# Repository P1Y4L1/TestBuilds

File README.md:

# TestBuilds
These are my PCB Test Builds which will updated , if intrested you are free to browse and fork from it.

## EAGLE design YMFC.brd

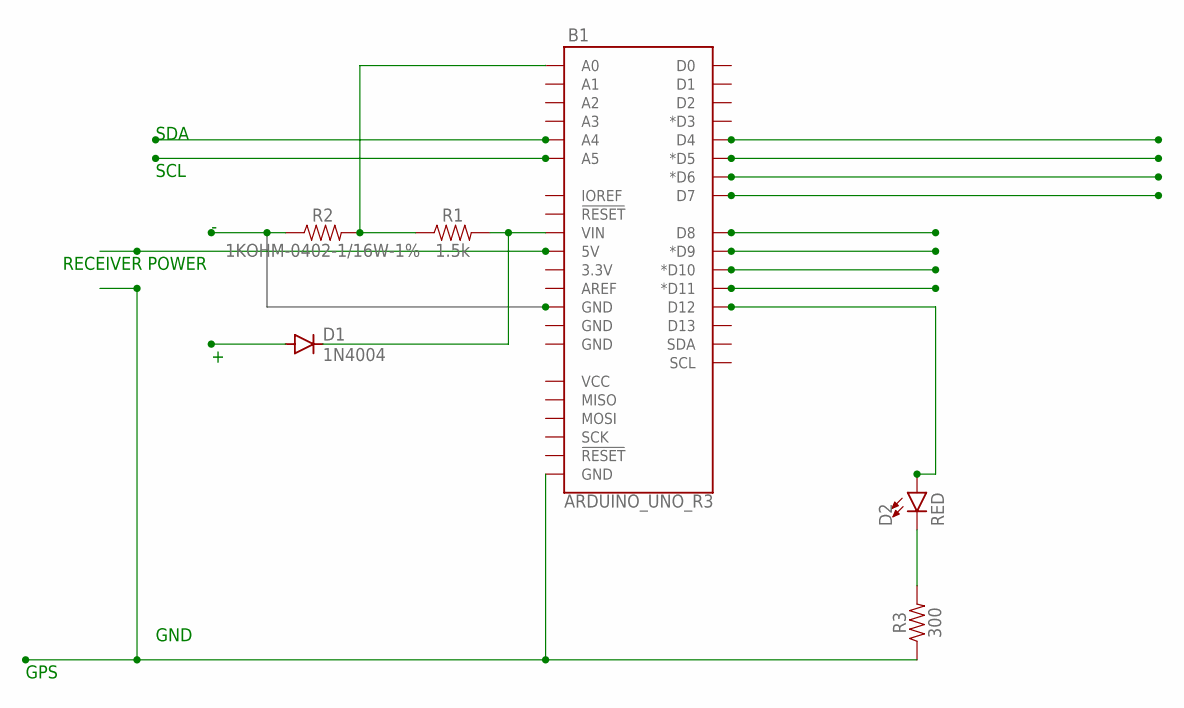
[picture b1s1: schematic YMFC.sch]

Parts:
B1: ARDUINO_UNO_R3; ARDUINO_R3
D1: 1N4004; DO41-10
D2: RED; LED-0603
R1: 1.5k; 0603
R2: 1KOHM-0402-1/16W-1%; 0402
R3: 300; 0603

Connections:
unnamed: B1.VIN, D1.C, R1.2
unnamed: B1.A0, R1.1, R2.2
unnamed: B1.D12, D2.A
unnamed: D2.C, R3.2
unnamed: B1.GND@1 (GND), R3.1

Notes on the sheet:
SDA
SCL
RECEIVER POWER
GND
GPS

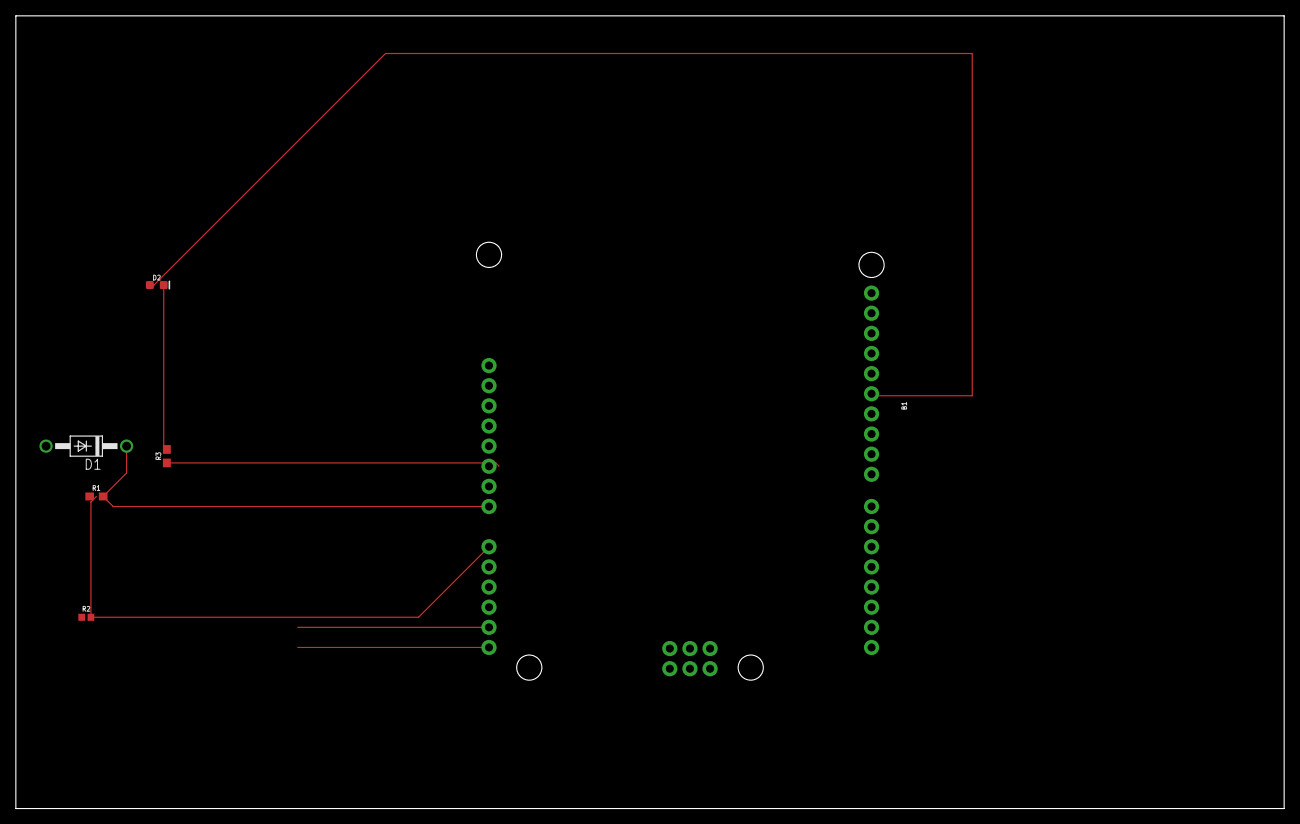
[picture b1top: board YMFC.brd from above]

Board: 2 copper layers, 160.0 x 100.0 mm, 6 parts (0 on the bottom side), 5 nets.

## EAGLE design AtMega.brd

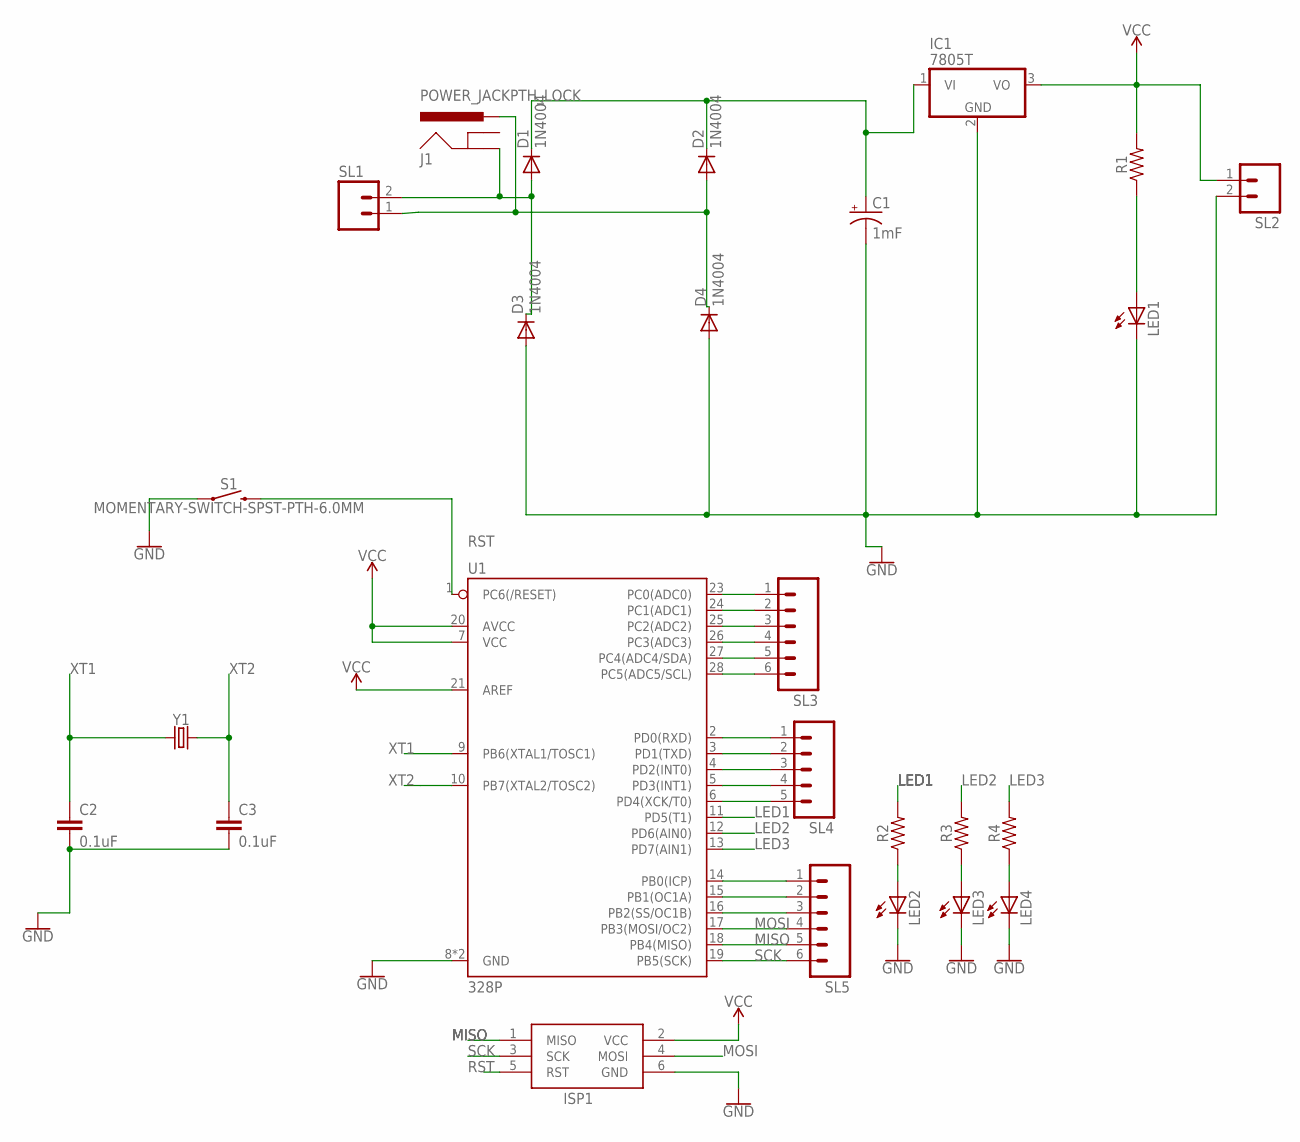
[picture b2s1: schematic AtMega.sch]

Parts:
C1: 1mF; CPOL-RADIAL-5MM-10MM
C2, C3: 0.1uF; CAP-PTH-SMALL-KIT
D1, D2, D3, D4: 1N4004; DO41-10
IC1: 7805T; TO220H
ISP1: AVRISP-6; AVRISP
J1: POWER_JACKPTH_LOCK; POWER_JACK_PTH_LOCK
LED1: LED5MM
LED2, LED3, LED4: LED3MM
R1, R2, R3, R4: AXIAL-0.3
S1: MOMENTARY-SWITCH-SPST-PTH-6.0MM; TACTILE_SWITCH_PTH_6.0MM
SL1, SL2: M02; 02P
SL3, SL5: M06; 06P
SL4: M05; 05P
U1: 328P; DIP28
Y1: CRYSTALPTH-HC49US; HC49US

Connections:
GND: C1.-, C2.2, C3.2, D3.A, IC1.2 (GND), ISP1.6 (GND), LED1.K (C), LED2.K (C), LED3.K (C), LED4.K (C), S1.1, SL2.2, U1.8 (GND), U1.22 (GND)
LED1: R2.P$2 (2), U1.11 (PD5(T1))
LED2: R3.P$2 (2), U1.12 (PD6(AIN0))
LED3: R4.P$2 (2), U1.13 (PD7(AIN1))
MISO: ISP1.1 (MISO), SL5.5, U1.18 (PB4(MISO))
MOSI: ISP1.4 (MOSI), SL5.4, U1.17 (PB3(MOSI/OC2))
unnamed: D2.A, D4.C, J1.PWR, SL1.1
unnamed: SL5.3, U1.16 (PB2(SS/OC1B))
unnamed: LED4.A, R4.P$1 (1)
unnamed: C1.+, D1.C, D2.C, IC1.1 (VI)
unnamed: D1.A, D3.C, SL1.2
unnamed: LED1.A, R1.P$1 (1)
unnamed: LED3.A, R3.P$1 (1)
unnamed: LED2.A, R2.P$1 (1)
unnamed: SL3.1, U1.23 (PC0(ADC0))
unnamed: SL3.2, U1.24 (PC1(ADC1))
unnamed: SL3.3, U1.25 (PC2(ADC2))
unnamed: SL3.4, U1.26 (PC3(ADC3))
unnamed: SL3.5, U1.27 (PC4(ADC4/SDA))
unnamed: SL3.6, U1.28 (PC5(ADC5/SCL))
unnamed: SL4.1, U1.2 (PD0(RXD))
unnamed: SL4.2, U1.3 (PD1(TXD))
unnamed: SL4.3, U1.4 (PD2(INT0))
unnamed: SL4.4, U1.5 (PD3(INT1))
unnamed: SL4.5, U1.6 (PD4(XCK/T0))
unnamed: SL5.1, U1.14 (PB0(ICP))
unnamed: SL5.2, U1.15 (PB1(OC1A))
RST: ISP1.5 (RST), S1.3 (2), U1.1 (PC6(/RESET))
SCK: ISP1.3 (SCK), SL5.6, U1.19 (PB5(SCK))
VCC: IC1.3 (VO), ISP1.2 (VCC), R1.P$2 (2), SL2.1, U1.7 (VCC), U1.20 (AVCC), U1.21 (AREF)
XT1: C2.1, U1.9 (PB6(XTAL1/TOSC1)), Y1.1
XT2: C3.1, U1.10 (PB7(XTAL2/TOSC2)), Y1.2

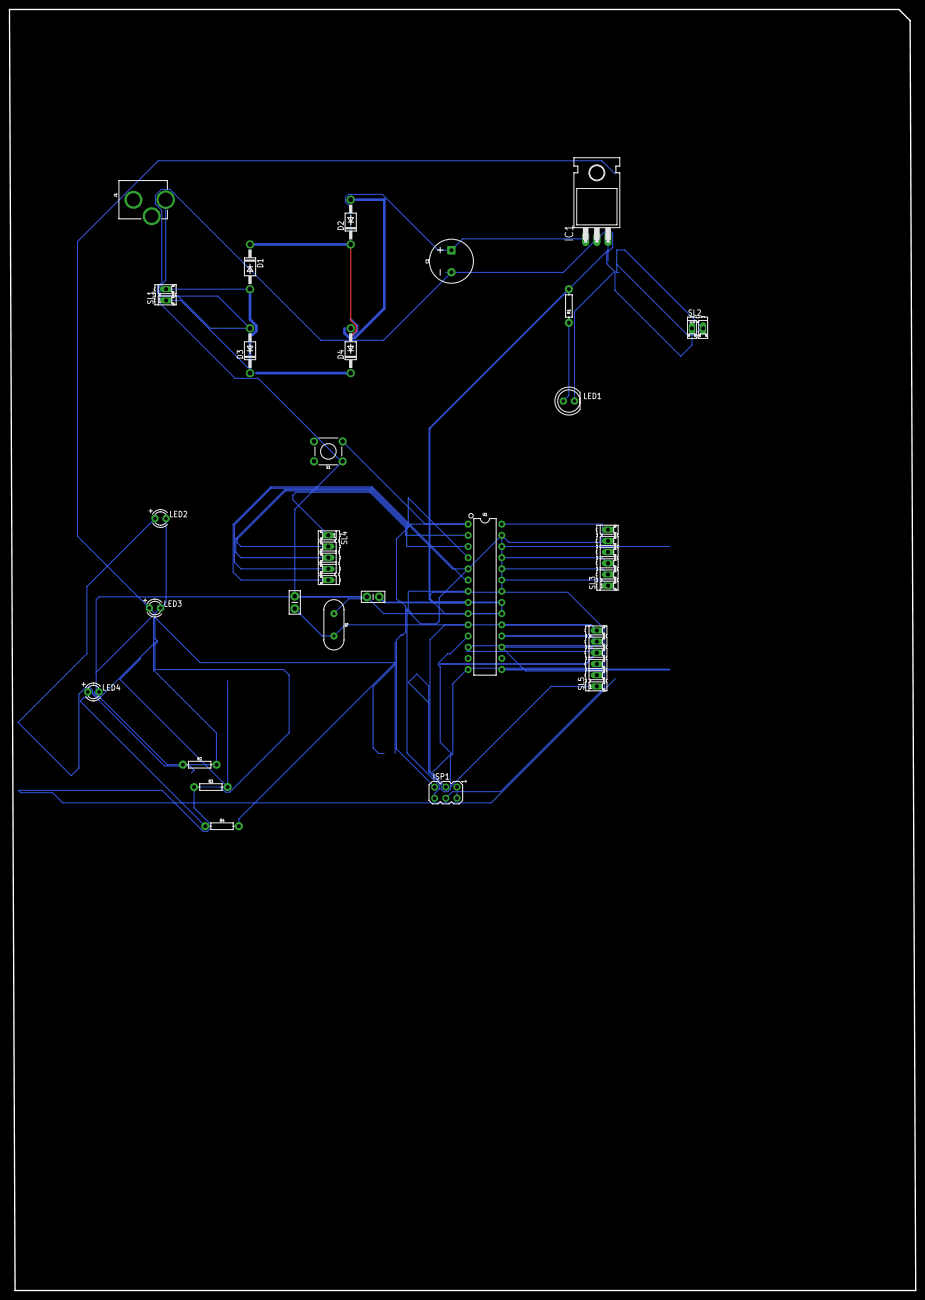
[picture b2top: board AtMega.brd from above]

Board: 2 copper layers, 205.7 x 290.8 mm, 26 parts (0 on the bottom side), 32 nets.

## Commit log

2020-02-01 Create BuzzerTester
    This code is almost like a proximity detector where a IR Sensor , if detects change in variable value, gives an output from a buzzer
    || instructions ||
    >Connect D0 or Input of the IR to 7th Digital Pin to the Arduino Board
    >BLAH BLAH!!!
2020-02-01 Add files via upload
    The eagle schematics uploaded above are related to ATmega microcontroller board and basic voltage regulation device of 7805T .
    Further updates will be given in the future , this is just a start!

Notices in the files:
parts and their libraries:
SparkFun-Capacitors: Licensing: Creative Commons ShareAlike 4.0 International - https://creativecommons.org/licenses/by-sa/4.0
